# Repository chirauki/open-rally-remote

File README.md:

# Open Rally Remote

> Spanish version: [README.es.md](README.es.md).

An open-source Bluetooth handlebar remote for motorcycle navigation and digital roadbooks. The project aims to keep the unit compact, rugged, affordable, and buildable one unit at a time by individual makers.

## Designed with AI

This project is a demonstration that large language models and AI agents let a person design a product from scratch without the engineering background it would normally need. The remote started from the needs of a rider who is not an electronics, mechanical or firmware engineer. AI assistants (ChatGPT and Claude) designed it from there: the requirements, the CAD models, the circuit boards, the firmware, the bill of materials and this documentation.

The person sets the goals, makes the decisions, buys the parts and tests on the bench; the AI does the engineering work, checks its own designs in CAD, KiCad and on the bench, and records what has and has not been verified. The design history in [docs/](docs/) and the commit log show how each decision was reached.

## Project status

Requirements and the first-version concept are being defined. No hardware design or compatibility claim has been validated yet.

See the [project brief](docs/project-brief.md) for the current goals, proposed design, constraints, and development plan. The current [control mapping draft](docs/control-mapping.md) records proposed app profiles and the compatibility checks still needed. The [prototype plan](docs/prototype-plan.md) compares controller candidates and lays out a bench proof of concept. The [XIAO breadboard assembly guide](docs/breadboard-assembly.md) gives the wiring diagram for the temporary input fixture.

The proposed [firmware specification](docs/firmware-spec.md) defines the first BLE HID approach, input and gesture behavior, app-profile boundaries, bench validation, and the product requirement for phone-based BLE firmware updates.

The [development environment guide](docs/development-environment.md) explains how to set up Arduino IDE 2 for the purchased XIAO nRF52840, upload a smoke-test sketch, and use the Serial Monitor. The [mechanical CAD notes](docs/mechanical-concept.md) document the current NAVCOMM-referenced concept: a battery-powered remote that slides onto a base clamped to the bar, raised external controls, and 25 mm along the bar (since V0.33; NAVCOMM's 23 mm is a reference). V0.26 can be built without soldering: assembled boards, bought cables, a TPU keypad and a plug-in XIAO. The boards can also be ordered bare and soldered by hand, for much less ([ordering the boards](docs/bom.md#ordering-the-boards)). V0.27 changes the joystick board so the housing closes onto the stack in a straight line, which V0.26's [path check](docs/assembly-video-v0.26-checks.md) found it could not. V0.28 fits one base to both bar sizes and moves the vent to the battery cap. V0.29 drops the heat-set inserts, so the build needs no hot tool. V0.30 seals the cover with a foam strip, because the keypad sheet could not be squeezed enough by M2 screws, and V0.31 seals the battery cap the same way. V0.32 cuts the number of different parts to buy: a standard M3 × 20 lock screw, anti-rattle strips cut from a bike inner tube, and foam pads from the seal foam. V0.33 thickens the remote's 1 mm walls to 2 mm, outward, for falls and for watertight prints; the cavity does not change. V0.34 follows the first soldered USB-C board, whose receptacle sits 0.3 mm off the screw holes: the board slides on its rib onto square nuts, so the gasket sets its squeeze, and goes in upside down so a driver reaches its screws through the battery cap opening; and the foam seals take two layers of the thinner sheet that was bought. An [assembly video](docs/videos/complete-remote-v0.34-assembly.mp4) with a [path check](docs/assembly-video-v0.34-checks.md) shows the V0.34 steps with no collisions, and a [fitting video](docs/videos/usbc-mount-v0.34.mp4) shows the USB-C board step in detail.

The [battery study](docs/battery-study.md) compares battery options and settles on a removable remote with a fixed LiPo pouch, shared between bikes on a sliding dovetail base and charged off the bike (issue #1). V0.24 models it, V0.25 moves the pouch to a battery cap in the bottom end, and V0.26 fits it protection board up so its lead plugs straight into the control board; see the [mechanical CAD notes](docs/mechanical-concept.md). Nothing of it has been built or measured.

The [build guide](docs/build-guide.md) takes a builder from this repository to a finished remote, in order, with the catches found so far: minimum orders, packs and import charges. It has not been tried on a build yet. The [user manual](docs/user-manual.md) explains how to use the finished remote: charging, pairing, profiles and what each control does. The [bill of materials](docs/bom.md) lists every part for the bench prototype, the remote and the base, with sources. The [materials study](docs/materials-study.md) compares print materials against sun, rain, fuel, cold and falls, with quotes from EU print services; the material is not chosen yet. The [electronics assembly guide](docs/electronics-assembly.md) takes the bare boards through hand soldering, tests and conformal coating, step by step with images; it has not been tried on a build yet.

V0.31 to V0.34 have three KiCad boards, each with Gerbers, a BOM and a placement file for assembly: the [control board](electronics/control-pcb/README.md) (buttons, plug-in XIAO, charger, regulator, sockets), the [joystick board rev C](electronics/joystick-pcb-rev-c/README.md) and the [USB-C charging board rev B](electronics/usbc-pcb-rev-b/README.md). The control and joystick boards are ordered together as [one panel](electronics/panel-ctrl-joy/README.md). The [joystick board rev B](electronics/joystick-pcb-rev-b/README.md) belongs to V0.26, and the rev A [joystick](electronics/joystick-pcb/README.md) and [USB-C](electronics/usbc-pcb/README.md) boards to V0.23–V0.25. None has been built yet.

The [XIAO bench firmware](firmware/xiao-nrf52840/README.md) reads the breadboard switches and sends BLE HID keyboard keys. It reads the joystick center as a chord of the direction switches. It has three profiles, tested on Android: TerraPirata, a keyboard profile with held keys for DMD2, and a gestures profile for OsmAnd; holding the joystick center 5 s, releasing it, then pressing A, B or C chooses one. It has passed a first bench test on a XIAO with breadboard switches, paired with a phone. It has also been updated over BLE from an Android phone with the XIAO's factory bootloader, which accepts unsigned images and is not yet the product's update path. The battery firmware (level, charging, power off, auto-off and wake) is written and partly tested on USB; it has not run on a cell yet.

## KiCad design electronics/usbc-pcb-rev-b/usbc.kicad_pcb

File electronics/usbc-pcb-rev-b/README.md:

# USB-C Charging Board, Rev B (V0.26)

Rev B of the [USB-C charging board](../usbc-pcb/README.md) for the no-solder V0.26 remote ([spec](../../docs/superpowers/specs/2026-10-14-no-solder-assembly-design.md)). The GCT USB4736 receptacle, the two 5.1 kΩ CC pull-downs and the side-looking charge LED stay at their rev A positions against the rear wall. The changes:

- The wire pads become one JST SH-compatible 3-pin side-entry socket (J2, LCSC C2906269) behind the receptacle, opening into the remote toward the control board.
- The board is 16.0 mm deep instead of 13.6 mm, and the two M2 holes move from x = ±5.4 to ±7.0 mm, to make room for the socket. The CC resistors move beside the receptacle. `usbc_pcb` and `usbc_pcb_holes` in `mechanical/cad/complete-remote-v0.26.scad` follow.
- **Charge LED.** D1's anode goes to VBUS through R3 (1 kΩ); its cathode goes to J2 pin 3 and on to the charger's STAT pin on the control board. STAT is low only while the cell charges, so the LED lights only then, powered from the charger, not the cell. About 3 mA at 5 V. The firmware no longer drives it.

| J2 pin | Signal |
|---|---|
| 1 | VBUS |
| 2 | GND |
| 3 | LED cathode (to the charger's STAT) |

J2 has the same order as J3 on the control board, for a straight double-ended 3-pin JST SH cable. Check that the bought cable is straight.

The receptacle is in the JLCPCB library only through global sourcing (C9900206672), with no JLCPCB stock on 2026-10-14; on 2026-10-15 JLCPCB could not source it for an order. C9900206672 is the USB4736-GF-A without the gasket. Buy the USB4736-GF-A-KIT (receptacle and USBTJ-06 gasket) from TME or DigiKey and solder it by hand; leave J1 unselected in an assembly order. The gasket goes on after the receptacle is soldered.

## Next revision

The next revision is planned at 1.6 mm, with the rib lowered 0.4 mm. It should also power the LED from 3V3, so the firmware can use it as a status light without a charger, through a 4-pin J2. See the open unknowns in the [mechanical notes](../../docs/mechanical-concept.md#open-unknowns-before-printing).

## Receptacle footprint

`orr:GCT_USB4736` was drawn by hand from GCT's drawing USB4736, revision A, 9 April 2025, sheet 1, "Recommended PCB Layout". Checked against that drawing on 2026-10-14:

| Feature | Drawing | Footprint |
|---|---|---|
| Signal pads: width; centres across | 0.80 (B12, A12), 0.76 (B9, A9), 0.70 (A5, B5); ±2.75, ±1.52, ±0.50 | Same |
| Signal pads: length; distance from the PCB edge | 1.90; 5.50–7.40 (1.40 + 2.90 + 3.10) | Same. Until this check, the pads sat at 5.40–7.30 mm, 0.10 mm toward the edge |
| Shell slots: centres; drill; pad | ±4.895 (9.79 apart), 1.40 and 4.30 from the edge; 0.50 × 1.20; 1.10 × 1.80 | Same |
| Locating holes | Ø0.95, ±3.25 (6.50 apart), 4.30 from the edge | Same |
| Pin order, seen from the top | B12, B9, A5, B5, A9, A12, left to right | Same |
| Nose past the PCB edge | 1.70 (3.10 from the nose to the first shell slot, less 1.40) | 1.70 |

The terminal feet (bottom view: 2.20 to 2.60 mm behind the locating posts, so 6.50–6.90 mm from the edge) sit inside the pads either way. Check again against the footprint JLCPCB uses for the global-sourcing part (C9900206672) when ordering.

## Regenerating and checks

`gen_pcb.py` and `gen_sch.py` are shared with the control board: run `gen_pcb.py` with KiCad's Python, then the ERC, DRC and export commands in the [control board README](../control-pcb/README.md#regenerating), with `usbc` in place of `control`.

On 2026-10-14, again after the footprint fix: ERC 0 errors; DRC with schematic parity 0 errors and 0 unconnected pads (the remaining warnings say only that kicad-cli has no library tables).

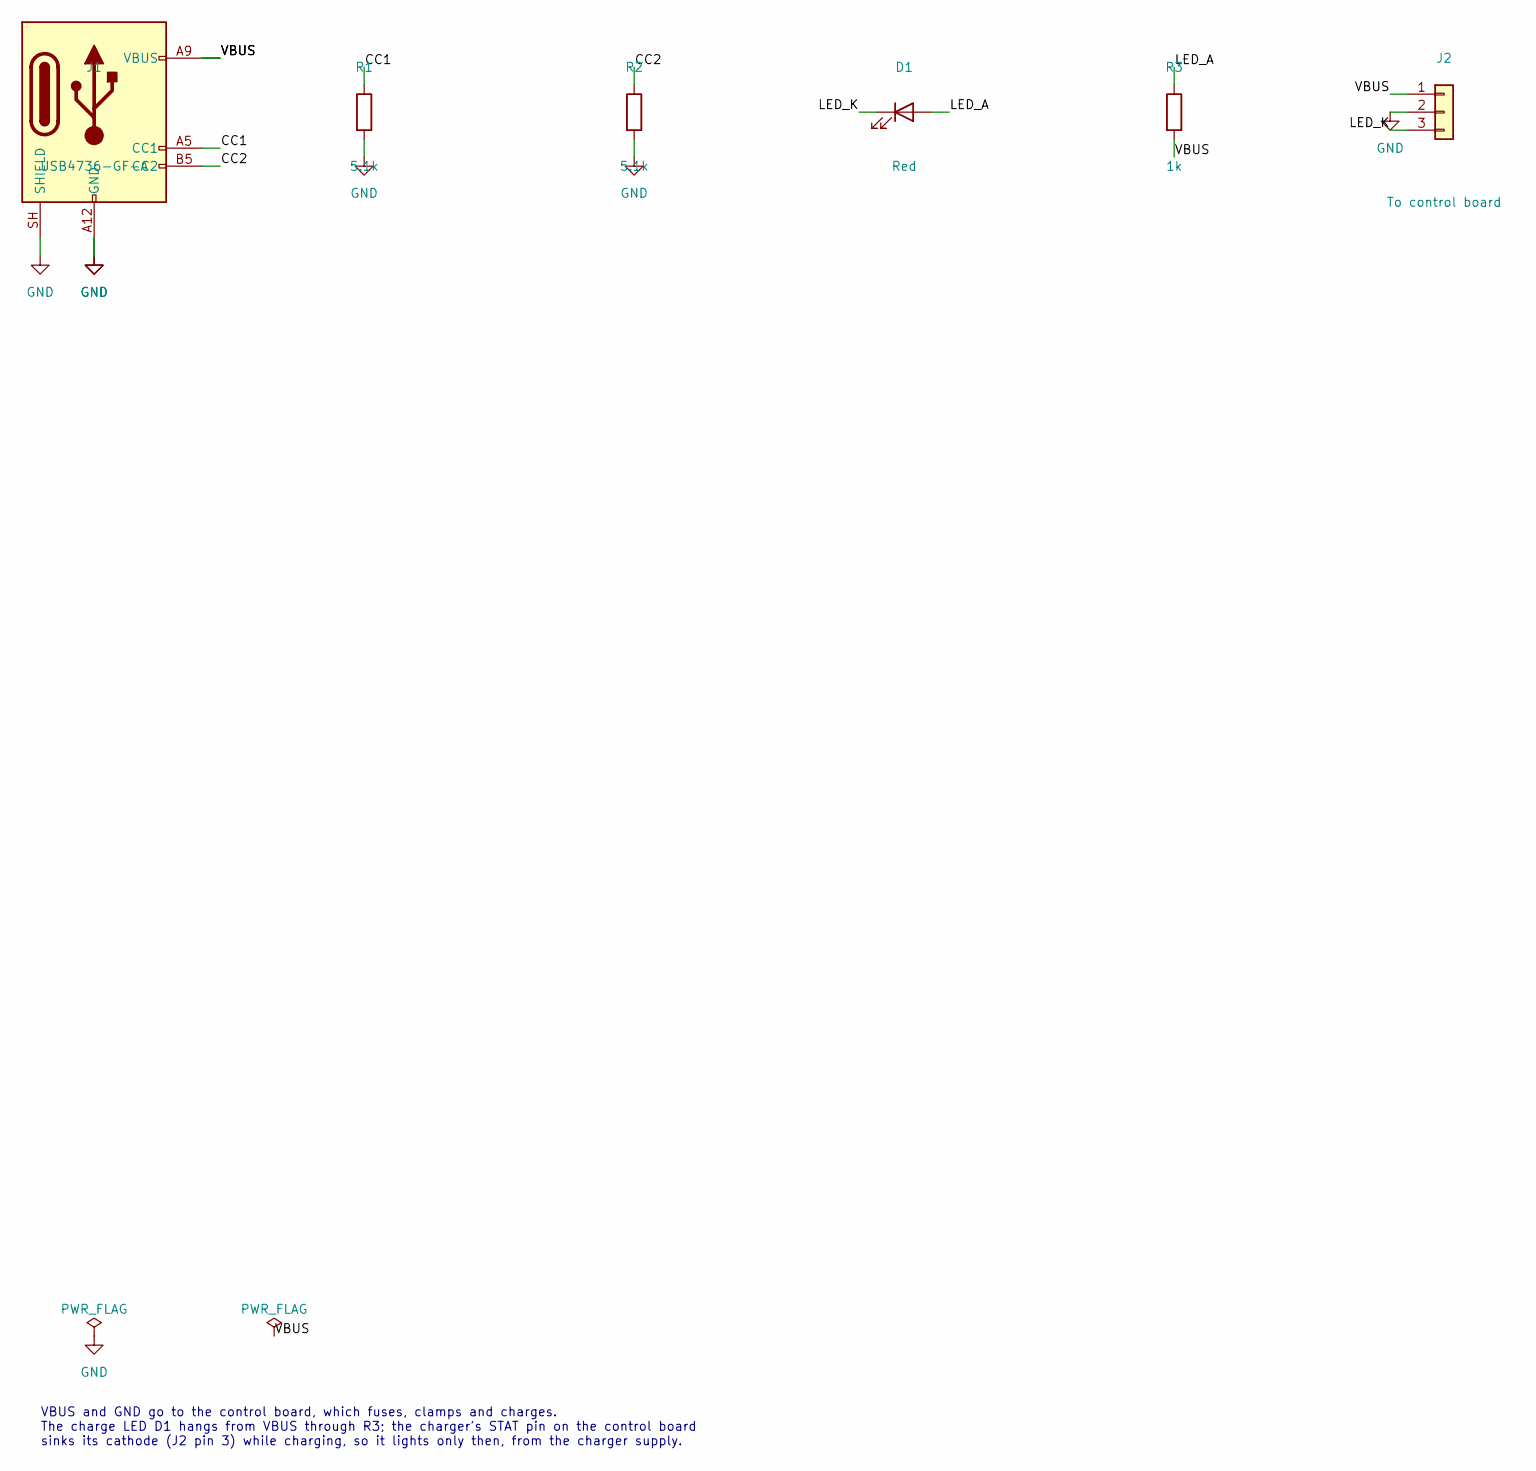
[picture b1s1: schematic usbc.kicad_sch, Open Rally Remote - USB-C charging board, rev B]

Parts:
D1: Red; LED_LiteOn_LTST-S270; MPN LTST-S270KRKT; LCSC C125114
J1: USB4736-GF-A; GCT_USB4736; MPN USB4736-GF-A-KIT; LCSC C9900206672
J2: To control board; JST_SH_SM03B-SRSS-TB_1x03-1MP_P1.00mm_Horizontal; MPN 1.0-3P WT; LCSC C2906269
R1, R2: 5.1k; R_0603_1608Metric; MPN 0603WAF5101T5E; LCSC C23186
R3: 1k; R_0603_1608Metric; MPN RC0603FR-071KL; LCSC C22548

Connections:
/CC1: J1.A5 (CC1), R1.1
/CC2: J1.B5 (CC2), R2.1
/LED_A: D1.2 (A), R3.1
/LED_K: D1.1 (K), J2.3
/VBUS: J1.A9 (VBUS), J1.B9 (VBUS), J2.1, R3.2
GND: J1.A12 (GND), J1.B12 (GND), J1.SH (SHIELD), J2.2, R1.2, R2.2

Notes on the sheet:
VBUS and GND go to the control board, which fuses, clamps and charges. The charge LED D1 hangs from VBUS through R3; the charger's STAT pin on the control board sinks its cathode (J2 pin 3) while charging, so it lights only then, from the charger supply.

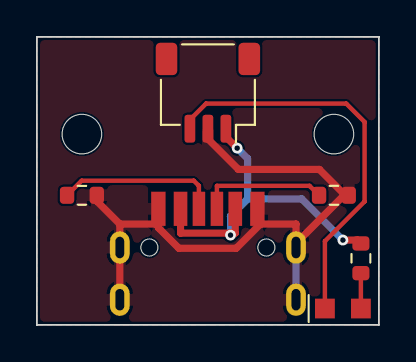
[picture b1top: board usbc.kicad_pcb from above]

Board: 2 copper layers, 19.0 x 16.0 mm, 8 parts (0 on the bottom side), 6 nets.

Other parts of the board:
H1, H2: M2; MountingHole_2.2mm_M2

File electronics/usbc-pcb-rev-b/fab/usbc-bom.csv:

"Reference","Value","Footprint","Manufacturer","MPN","LCSC","Qty"
"D1","Red","orr:LED_LiteOn_LTST-S270","Lite-On","LTST-S270KRKT","C125114","1"
"J1","USB4736-GF-A","orr:GCT_USB4736","GCT","USB4736-GF-A-KIT","C9900206672","1"
"J2","To control board","Connector_JST:JST_SH_SM03B-SRSS-TB_1x03-1MP_P1.00mm_Horizontal","","1.0-3P WT","C2906269","1"
"R1,R2","5.1k","Resistor_SMD:R_0603_1608Metric","UNI-ROYAL","0603WAF5101T5E","C23186","2"
"R3","1k","Resistor_SMD:R_0603_1608Metric","YAGEO","RC0603FR-071KL","C22548","1"

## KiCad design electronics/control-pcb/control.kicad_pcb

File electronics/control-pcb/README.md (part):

# Control Board (V0.26)

The control board sits behind the upper facet of the V0.26 remote. Its front carries the three button switches; its back carries the XIAO nRF52840 in two female headers, the LiPo charger, the 3.3 V regulator and the connectors for the joystick board, the USB-C charging board and the battery. It can be ordered assembled, so the builder does not solder, or bare, for the builder to solder by hand; see [Ordering the boards](../../docs/bom.md#ordering-the-boards). `fab/economic-bottom/` holds the BOM and placement for JLCPCB Economic assembly of the back side only; the builder then solders the switches and the headers. The design is in the [no-solder assembly spec](../../docs/superpowers/specs/2026-10-14-no-solder-assembly-design.md).

## Parts

Checked in the JLCPCB parts library on 2026-10-14. Stock and prices change; check again before ordering. "Extended" parts add JLCPCB's extended-part fee per unique part.

| Function | Part | LCSC | Library | Stock | Notes |
|---|---|---|---|---|---|
| Button switches ×3 | C&K KSC221JLFS | C221726 | Extended | 17,354 | Same switch as the joystick board |
| LiPo charger | Microchip MCP73831T-2ACI/OT, SOT-23-5 | C424093 | Extended | 11,479 | 4.20 V. Charge current 1000 V / R_PROG: 10 kΩ gives 100 mA. STAT is low while charging, high when done, high-impedance with no input |
| 3.3 V regulator | TI TPS70933DBVR, SOT-23-5 | C89347 | Extended | 45,791 | 1 µA quiescent, 2.7–30 V input, reverse current protection ([TI](https://www.ti.com/product/TPS709)), 300 mV typical dropout |
| Battery reverse-polarity protection | AO3401A P-MOSFET, SOT-23 | C15127 | Basic | 605,007 | In the battery line, conducting both ways when the cell is the right way round |
| 5 V input fuse | Bourns MF-MSMF050-2, 1812 PTC | C17313 | — | — | As on the V0.23 joystick board |
| 5 V input TVS | Littelfuse SMBJ5.0A | C83333 | Extended | 45,298 | 65 µA leakage at 5 V; the other SMBJ5.0A listed, C78423, leaks 800 µA (both checked 2026-10-15) |
| Joystick socket (5-pin) | JST SH-compatible "1.0-5P WT", side entry, SMD | C2906271 | Extended | 14,999 | Genuine SM05B-SRSS-TB: C136657, 158 in stock |
| USB-C board socket (3-pin) | JST SH-compatible "1.0-3P WT", side entry, SMD | C2906269 | Extended | 13,209 | Genuine SM03B-SRSS-TB: none in stock |
| Battery socket (2-pin) | JST B2B-PH-SM4-TB(LF)(SN), top entry, SMD | C160352 | Extended | 89,576 | Side entry (S2B-PH-SM4-TB, C295747) was dropped: its plug had no room toward the wall |
| XIAO headers ×2 | 2.54 mm 1×7 female, 5.7 mm high, through hole | C55218877 | Extended | 644 | Standard 8.5 mm alternative: C54876729, 2,409 in stock |

The XIAO nRF52840 is in the JLCPCB library (C37327670 and others) with no stock, so the XIAO is bought separately with pins and plugged in. The PTC and TVS stock was not rechecked.

### USB-C charging receptacle

The GCT USB4736-GF-A is listed in the JLCPCB library only through global sourcing (C9900206672), with no JLCPCB stock on 2026-10-14. On 2026-10-15 JLCPCB could not source it for an order. C9900206672 is the receptacle without its USBTJ-06 gasket; buy the USB4736-GF-A-KIT (receptacle and gasket) from TME or DigiKey and solder it by hand. No other sealed receptacle that keeps the CC pins was found in the library.

### Cables

Retail, pre-crimped at both ends. Amazon listings were not found through web search; that does not mean there are none.

| Cable | Source found | Length |
|---|---|---|
| JST SH-style 5-pin, female–female, 1 mm | [Pololu 5-pin JST SH-style cables](https://www.pololu.com/category/350/5-pin-jst-sh-style-cables) | 10 cm shortest |
| JST SH-style 3-pin, female–female, 1 mm | Pololu's 3-pin range (not checked) | 10 cm shortest |
| JST PH 2-pin extension, male–female | [BerryBase](https://www.berrybase.de/en/extension-cable-2-pin-jst-ph-2.0mm-male-female-awg24-50cm) | 50 cm; shorter not found |

The routes need about 3 cm (joystick) and 4 cm (USB-C). The spare length of a 10 cm cable has to be stowed inside; the CAD checks this. The "1.0 WT" sockets are sold as JST SH compatible; check that a Pololu plug latches in one before ordering the board.

### XIAO pins

The board position depends on the pre-soldered XIAO's header: the plastic spacer height and the pin length below it. Neither is published by Seeed; measure them on the bench XIAO. A pin longer than the 5.7 mm socket is deep holds the XIAO higher than the spacer would.

## Circuit decisions

- **STAT to the XIAO.** The MCP73831's STAT is a three-state push-pull output: low while charging, high (about VDD − 0.4 V, so about 4.6 V from USB-C) when charging ends, high impedance with no input. D8 reads it through a 100 kΩ / 150 kΩ divider: at most about 2.8 V. The charge LED on the USB-C board hangs from VBUS to STAT through its resistor, so it lights only while STAT is low (charging).
- **VBUS to the XIAO.** D9 reads VBUS through a 100 kΩ / 150 kΩ divider: 3.0 V at 5.0 V, 3.15 V at 5.25 V. (Until the 2026-10-15 review it was 100k/200k, 3.3–3.5 V: with a low cell the XIAO's 3V3 rail sits near 3.0 V, and the nRF52840's pin limit is VDD + 0.3 V.)
- **Battery voltage.** A0 reads the cell through a 1 MΩ / 1 MΩ divider with 100 nF to ground: 2.1 V at 4.2 V, about 2 µA drawn from the cell.
- **Different socket sizes.** The joystick socket has 5 pins, the USB-C one 3 and the battery one is a 2-pin PH: no cable fits the wrong socket.

## Next revision

The next revision should add an N-MOSFET from the charging LED's cathode to GND, driven by D7, and a 4-pin J3 that also carries 3V3 to the USB-C board, so the firmware can pulse the LED as a status light without a charger. STAT keeps lighting it while charging. See the open unknowns in the [mechanical notes](../../docs/mechanical-concept.md#open-unknowns-before-printing).

## Review

An independent review on 2026-10-15 (a fresh Claude session reading the files and the TI SBVS186H, Microchip DS20001984H and AOS AO3401A datasheets) found no critical defect. It changed R3/R5 to 150k, C3/C4 to 4.7 µF (the TPS709 needs 1.5 µF effective at its output) and D1 to the low-leakage SMBJ5.0A, and raised the open points listed under Checks. Not verified by it: the XIAO regulator's reverse leakage and its 3V3-rail capacitance, the System OFF current, the KSC2 internal contact pairs, and the LED's cathode pad against the Lite-On drawing.

## Board

A 21.4 × 49 mm, 1.6 mm two-layer board, notched round the six upper cover-screw bosses so it lifts out with the cover (see `ctrl_pcb_*` in `mechanical/cad/complete-remote-v0.26.scad`). Board x is the CAD's Z − 11.5, board y is 16.5 − Y.

- **Front** (toward the cover): SW1–SW3 under keys A, B and C, at Y = 33, 15 and −3. Each switch uses a diagonal pad pair, as on the joystick board.
- **Back:** the two XIAO headers (pin 1 at the XIAO's USB-C end, D0–D6 on the −Z side), the charger, the regulator, Q1 and the dividers under the XIAO, J3 (USB-C board, side entry, opening down toward the USB-C board's socket) and J5 (battery, top entry: the pouch lead plugs in from behind, toward the pouch) at the top, J4 (joystick) at the bottom, F1 and D1 between them.
- **Holes:** two M2 holes onto the button plate standoffs, at Y = 24 and Y = 6, 3.95 mm either side of the centre line so the standoffs clear the key holes in the button plate.
- **Routing:** Freerouting 1.9.0, with ground pours on both layers. Track keep-outs round the notches hold the 0.3 mm edge clearance.

## Regenerating

`design.py` holds the outline, placement and nets. From this directory:

```
/Applications/KiCad/KiCad.app/Contents/Frameworks/Python.framework/Versions/Current/bin/python3 gen_pcb.py
```

`gen_pcb.py` places the parts, routes the board with Freerouting (`FREEROUTING_JAR`, default `~/.arduino-orr/tools/freerouting-1.9.0.jar`; Freerouting 2.x needs Java 25), fills the pours, writes `control.kicad_pcb` and calls `gen_sch.py` for `control.kicad_sch`. Freerouting may route differently on each run. Then check and export:

```
K=/Applications/KiCad/KiCad.app/Contents/MacOS/kicad-cli
$K sch erc --severity-all control.kicad_sch
$K pcb drc --schematic-parity --severity-all control.kicad_pcb
$K pcb export gerbers --layers F.Cu,B.Cu,F.Paste,B.Paste,F.SilkS,B.SilkS,F.Mask,B.Mask,Edge.Cuts --subtract-soldermask -o fab/gerbers/ control.kicad_pcb
$K pcb export drill --format excellon --excellon-separate-th --generate-map --map-format gerberx2 -o fab/gerbers/ control.kicad_pcb
$K sch export bom --fields 'Reference,Value,Footprint,Manufacturer,MPN,LCSC,${QUANTITY}' --labels 'Reference,Value,Footprint,Manufacturer,MPN,LCSC,Qty' --group-by 'Value,Footprint' --exclude-dnp -o fab/control-bom.csv control.kicad_sch
$K pcb export pos --format csv --units mm --side both --exclude-dnp -o fab/control-pos.csv control.kicad_pcb
python3 jlc_cpl.py
```

## Checks

Run on 2026-10-14, and again on 2026-10-15 after the J5 polarity marks and the review fixes (R3/R5 150k, C3/C4 4.7 µF, D1 C83333); same results, Freerouting routed it again:

- ERC: 0 errors. The 72 warnings say only that kicad-cli has no global symbol and footprint library tables configured.
- DRC with schematic parity: 0 errors, 0 unconnected pads, 0 footprint errors; the 22 warnings are the same library-table notice.
- **Battery plugged in reversed:** without USB, Q1's body diode is reverse-biased and its gate-source voltage stays at 0 V, so no current flows. With USB plugged in, the charger raises BAT_SYS until Q1 turns on and its preconditioning current (about 10 mA) flows into the reversed cell: not dangerous, but the cell slowly discharges and the charge LED lights. Unplug and turn the plug round.
- **XIAO's own USB-C plugged in with the battery in:** the XIAO's regulator drives 3V3 too; the TPS70933's reverse current protection stops current flowing back into it.
- **Charger with no battery:** the MCP73831 holds BAT_SYS near 4.2 V, so the remote runs on USB power alone. With no cell, the charger may cycle, and the charge LED and D8 may flicker; this was not checked.
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
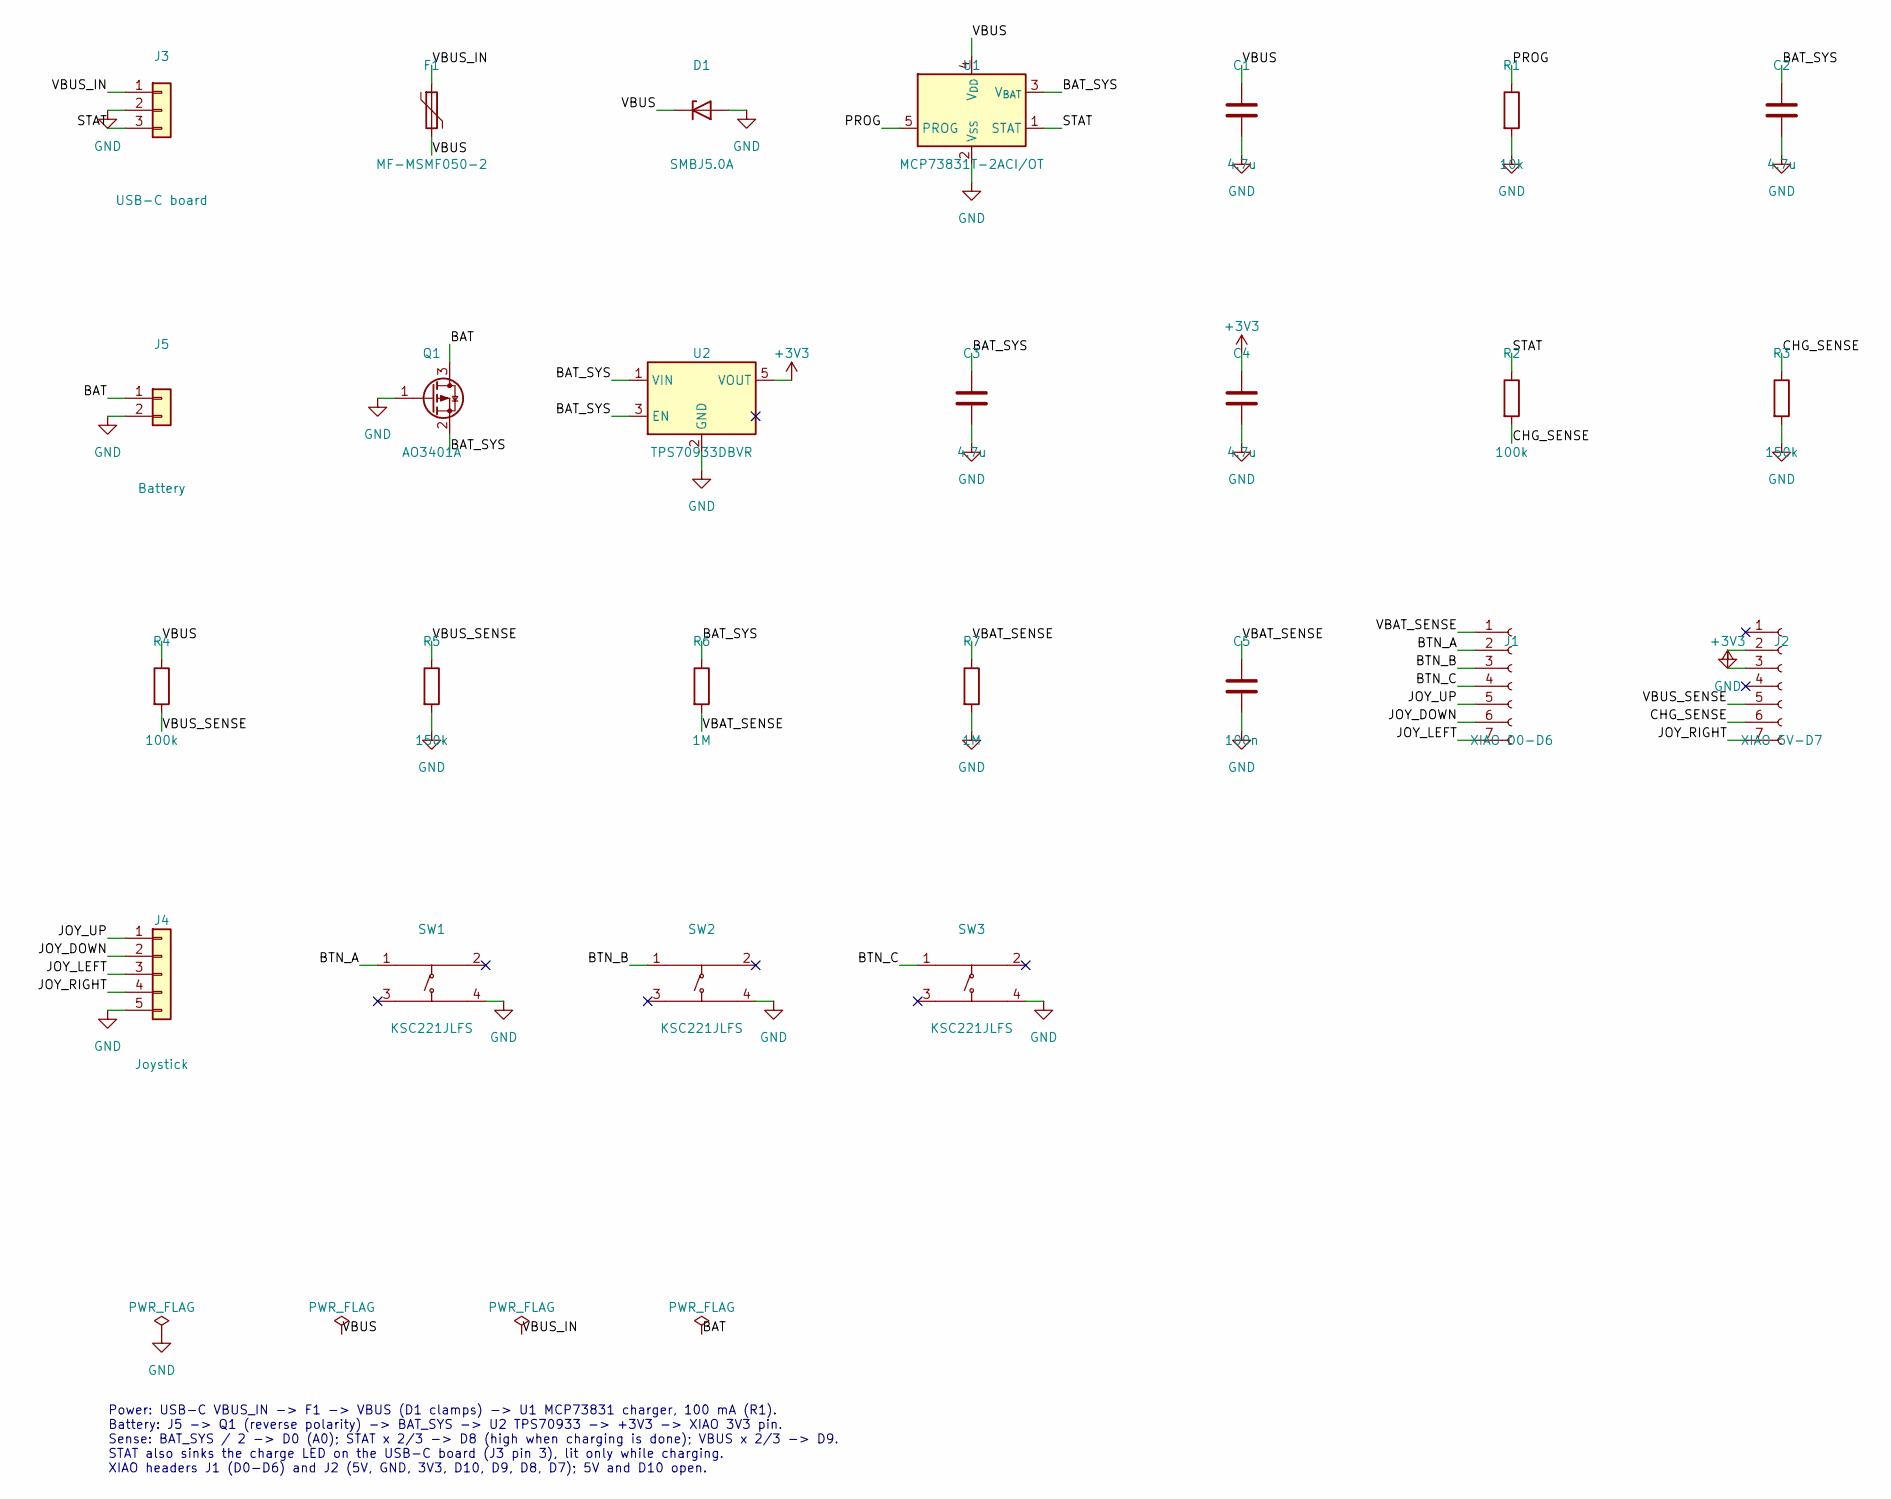
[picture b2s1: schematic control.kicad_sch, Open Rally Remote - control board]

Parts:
C1, C2, C3, C4: 4.7u; C_0603_1608Metric; MPN CL10A475KO8NNNC; LCSC C19666
C5: 100n; C_0603_1608Metric; MPN CC0603KRX7R9BB104; LCSC C14663
D1: SMBJ5.0A; D_SMB; MPN SMBJ5.0A; LCSC C83333
F1: MF-MSMF050-2; Fuse_1812_4532Metric; MPN MF-MSMF050-2; LCSC C17313
J1: XIAO D0-D6; PinSocket_1x07_P2.54mm_Vertical; MPN PM2.54-1x7PZZ-H5.7; LCSC C55218877
J2: XIAO 5V-D7; PinSocket_1x07_P2.54mm_Vertical; MPN PM2.54-1x7PZZ-H5.7; LCSC C55218877
J3: USB-C board; JST_SH_SM03B-SRSS-TB_1x03-1MP_P1.00mm_Horizontal; MPN 1.0-3P WT; LCSC C2906269
J4: Joystick; JST_SH_SM05B-SRSS-TB_1x05-1MP_P1.00mm_Horizontal; MPN 1.0-5P WT; LCSC C2906271
J5: Battery; JST_PH_B2B-PH-SM4-TB_1x02-1MP_P2.00mm_Vertical; MPN B2B-PH-SM4-TB(LF)(SN); LCSC C160352
Q1: AO3401A; SOT-23; MPN AO3401A; LCSC C15127
R1: 10k; R_0603_1608Metric; MPN 0603WAF1002T5E; LCSC C25804
R2, R4: 100k; R_0603_1608Metric; MPN 0603WAF1003T5E; LCSC C25803
R3, R5: 150k; R_0603_1608Metric; MPN 0603WAF1503T5E; LCSC C22807
R6, R7: 1M; R_0603_1608Metric; MPN 0603WAF1004T5E; LCSC C22935
SW1, SW2, SW3: KSC221JLFS; KSC2_SMD_6.2x6.2mm; MPN KSC221JLFS; LCSC C221726
U1: MCP73831T-2ACI/OT; SOT-23-5; MPN MCP73831T-2ACI/OT; LCSC C424093
U2: TPS70933DBVR; SOT-23-5; MPN TPS70933DBVR; LCSC C89347

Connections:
+3V3: C4.1, J2.3, U2.5 (VOUT)
/BAT: J5.1, Q1.3 (D)
/BAT_SYS: C2.1, C3.1, Q1.2 (S), R6.1, U1.3 (V_{BAT}), U2.1 (VIN), U2.3 (EN)
/BTN_A: J1.2, SW1.1
/BTN_B: J1.3, SW2.1
/BTN_C: J1.4, SW3.1
/CHG_SENSE: J2.6, R2.2, R3.1
/JOY_DOWN: J1.6, J4.2
/JOY_LEFT: J1.7, J4.3
/JOY_RIGHT: J2.7, J4.4
/JOY_UP: J1.5, J4.1
/PROG: R1.1, U1.5 (PROG)
/STAT: J3.3, R2.1, U1.1 (STAT)
/VBAT_SENSE: C5.1, J1.1, R6.2, R7.1
/VBUS: C1.1, D1.1 (K), F1.2, R4.1, U1.4 (V_{DD})
/VBUS_IN: F1.1, J3.1
/VBUS_SENSE: J2.5, R4.2, R5.1
GND: C1.2, C2.2, C3.2, C4.2, C5.2, D1.2 (A), J2.2, J3.2, J4.5, J5.2, Q1.1 (G), R1.2, R3.2, R5.2, R7.2, SW1.4, SW2.4, SW3.4, U1.2 (V_{SS}), U2.2 (GND)

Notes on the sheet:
Power: USB-C VBUS_IN -> F1 -> VBUS (D1 clamps) -> U1 MCP73831 charger, 100 mA (R1). Battery: J5 -> Q1 (reverse polarity) -> BAT_SYS -> U2 TPS70933 -> +3V3 -> XIAO 3V3 pin. Sense: BAT_SYS / 2 -> D0 (A0); STAT x 2/3 -> D8 (high when charging is done); VBUS x 2/3 -> D9. STAT also sinks the charge LED 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

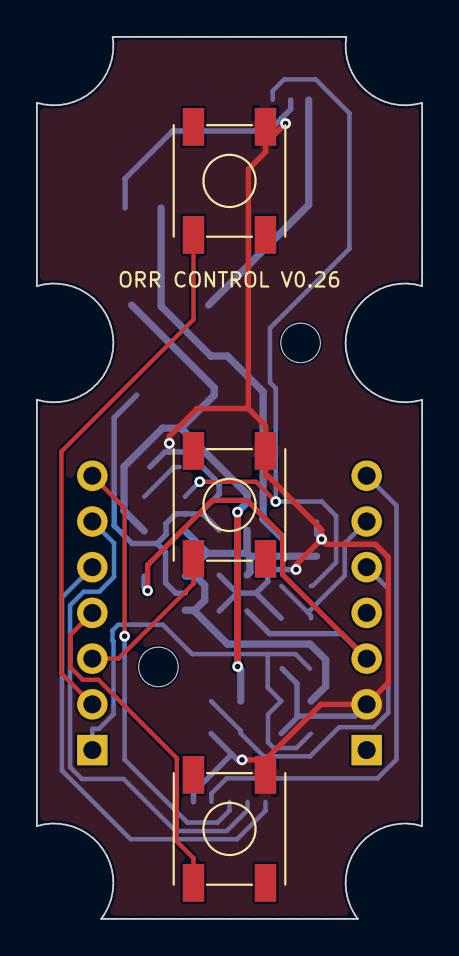
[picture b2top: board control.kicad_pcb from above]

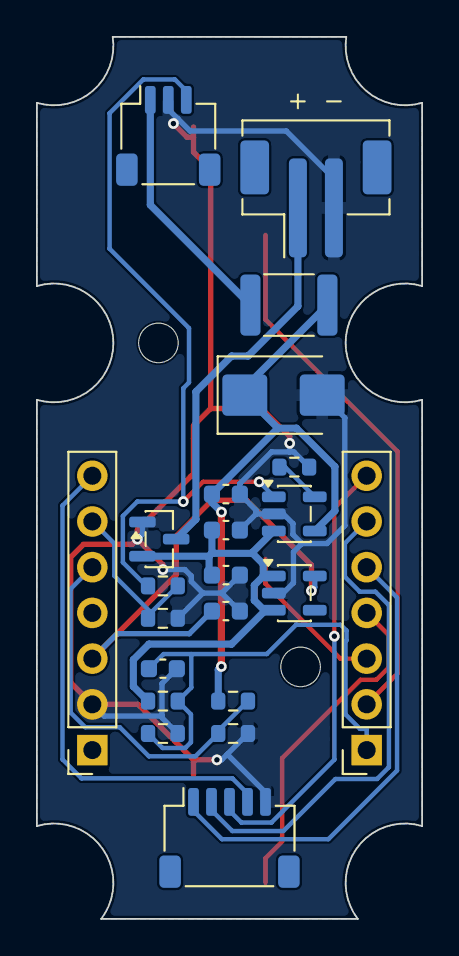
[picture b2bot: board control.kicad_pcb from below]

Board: 2 copper layers, 21.4 x 49.0 mm, 27 parts (22 on the bottom side), 18 nets.

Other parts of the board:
H1, H2: M2; Standoff_M2_PCB

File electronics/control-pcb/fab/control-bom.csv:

"Reference","Value","Footprint","Manufacturer","MPN","LCSC","Qty"
"C1-C4","4.7u","Capacitor_SMD:C_0603_1608Metric","Samsung","CL10A475KO8NNNC","C19666","4"
"C5","100n","Capacitor_SMD:C_0603_1608Metric","Yageo","CC0603KRX7R9BB104","C14663","1"
"D1","SMBJ5.0A","Diode_SMD:D_SMB","Littelfuse","SMBJ5.0A","C83333","1"
"F1","MF-MSMF050-2","Fuse:Fuse_1812_4532Metric","Bourns","MF-MSMF050-2","C17313","1"
"J1","XIAO D0-D6","Connector_PinSocket_2.54mm:PinSocket_1x07_P2.54mm_Vertical","","PM2.54-1x7PZZ-H5.7","C55218877","1"
"J2","XIAO 5V-D7","Connector_PinSocket_2.54mm:PinSocket_1x07_P2.54mm_Vertical","","PM2.54-1x7PZZ-H5.7","C55218877","1"
"J3","USB-C board","Connector_JST:JST_SH_SM03B-SRSS-TB_1x03-1MP_P1.00mm_Horizontal","","1.0-3P WT","C2906269","1"
"J4","Joystick","Connector_JST:JST_SH_SM05B-SRSS-TB_1x05-1MP_P1.00mm_Horizontal","","1.0-5P WT","C2906271","1"
"J5","Battery","Connector_JST:JST_PH_B2B-PH-SM4-TB_1x02-1MP_P2.00mm_Vertical","JST","B2B-PH-SM4-TB(LF)(SN)","C160352","1"
"Q1","AO3401A","Package_TO_SOT_SMD:SOT-23","Alpha & Omega","AO3401A","C15127","1"
"R1","10k","Resistor_SMD:R_0603_1608Metric","UNI-ROYAL","0603WAF1002T5E","C25804","1"
"R2,R4","100k","Resistor_SMD:R_0603_1608Metric","UNI-ROYAL","0603WAF1003T5E","C25803","2"
"R3,R5","150k","Resistor_SMD:R_0603_1608Metric","UNI-ROYAL","0603WAF1503T5E","C22807","2"
"R6,R7","1M","Resistor_SMD:R_0603_1608Metric","UNI-ROYAL","0603WAF1004T5E","C22935","2"
"SW1-SW3","KSC221JLFS","orr:KSC2_SMD_6.2x6.2mm","C&K","KSC221JLFS","C221726","3"
"U1","MCP73831T-2ACI/OT","Package_TO_SOT_SMD:SOT-23-5","Microchip","MCP73831T-2ACI/OT","C424093","1"
"U2","TPS70933DBVR","Package_TO_SOT_SMD:SOT-23-5","TI","TPS70933DBVR","C89347","1"

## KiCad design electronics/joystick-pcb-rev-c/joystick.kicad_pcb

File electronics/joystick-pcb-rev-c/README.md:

# Joystick Board, Rev C (V0.27)

Rev C of the joystick board, for V0.27. It is [rev B](../joystick-pcb-rev-b/README.md) with three changes, so the housing can close onto the stack, and the cover come off, in a straight line along the remote's X axis ([V0.27 changes from V0.26](../../docs/mechanical-concept.md#v027-changes-from-v026-still-current)):

- The two notches toward the fold (board y = −11.0) become slots running 3.0 mm down the facet (`SLOT` in `design.py`, `joy_pcb_slot` in the CAD). The lower cover bosses slide that way, 0.34 mm per millimetre, as the housing moves along X.
- The two standoff holes move to the lower half, at (±6.5, 6.4) in board coordinates. The upper half has no room for a screw between the switches and the slots.
- J1 moves from (1.0, 7.4) to (0.0, 7.4), to pass between the two screw heads.

The switches, the nets and the J1 pinout are those of rev B:

| J1 pin | Signal |
|---|---|
| 1 | UP |
| 2 | DOWN |
| 3 | LEFT |
| 4 | RIGHT |
| 5 | GND |

J1 has the same order as J4 on the control board, so a straight double-ended 5-pin JST SH cable (pin 1 to pin 1) joins them. Check that the bought cable is straight and not reversed before fitting it.

## Clearances

Board coordinates, mm, from `design.py` and the KiCad footprints:

| Between | Clearance |
|---|---|
| Slot edge and the nearest switch pad | 0.67 |
| Standoff (Ø3.6) and the nearest switch pad | 0.82 |
| Standoff and the nearest switch body | 1.35 |
| Standoff courtyard (R1.9) and the side-switch and J1 courtyards | 0.2 |
| Screw head (Ø3.5) and J1, each side | 0.35 |
| Standoff and the lower notch edge | 0.37 |

## Regenerating and checks

`design.py` builds the outline with the slots and holds the placement and nets. `gen_pcb.py` and `gen_sch.py` are shared with the control board: run `gen_pcb.py` with KiCad's Python, then the ERC, DRC and export commands in the [control board README](../control-pcb/README.md#regenerating), with `joystick` in place of `control`. The rear render is `kicad-cli pcb render --side bottom --width 1200 --height 900 -o fab/render-back.png joystick.kicad_pcb`.

On 2026-10-14: ERC 0 errors (the 9 warnings say only that kicad-cli has no library tables); DRC with schematic parity 0 errors and 0 unconnected pads (one library-table warning). Placing the standoffs at (±6.8, 6.0) first gave two courtyard overlaps with the side switches; (±6.5, 6.4) clears them. Full assembly is double-sided: switches on the front, the socket on the rear. `fab/economic-bottom/` holds the BOM and placement for JLCPCB Economic assembly of the rear side only (J1); the builder then solders the switches. The board can also be ordered bare and soldered by hand; see [Ordering the boards](../../docs/bom.md#ordering-the-boards). Check the parts' rotations in JLCPCB's placement preview.

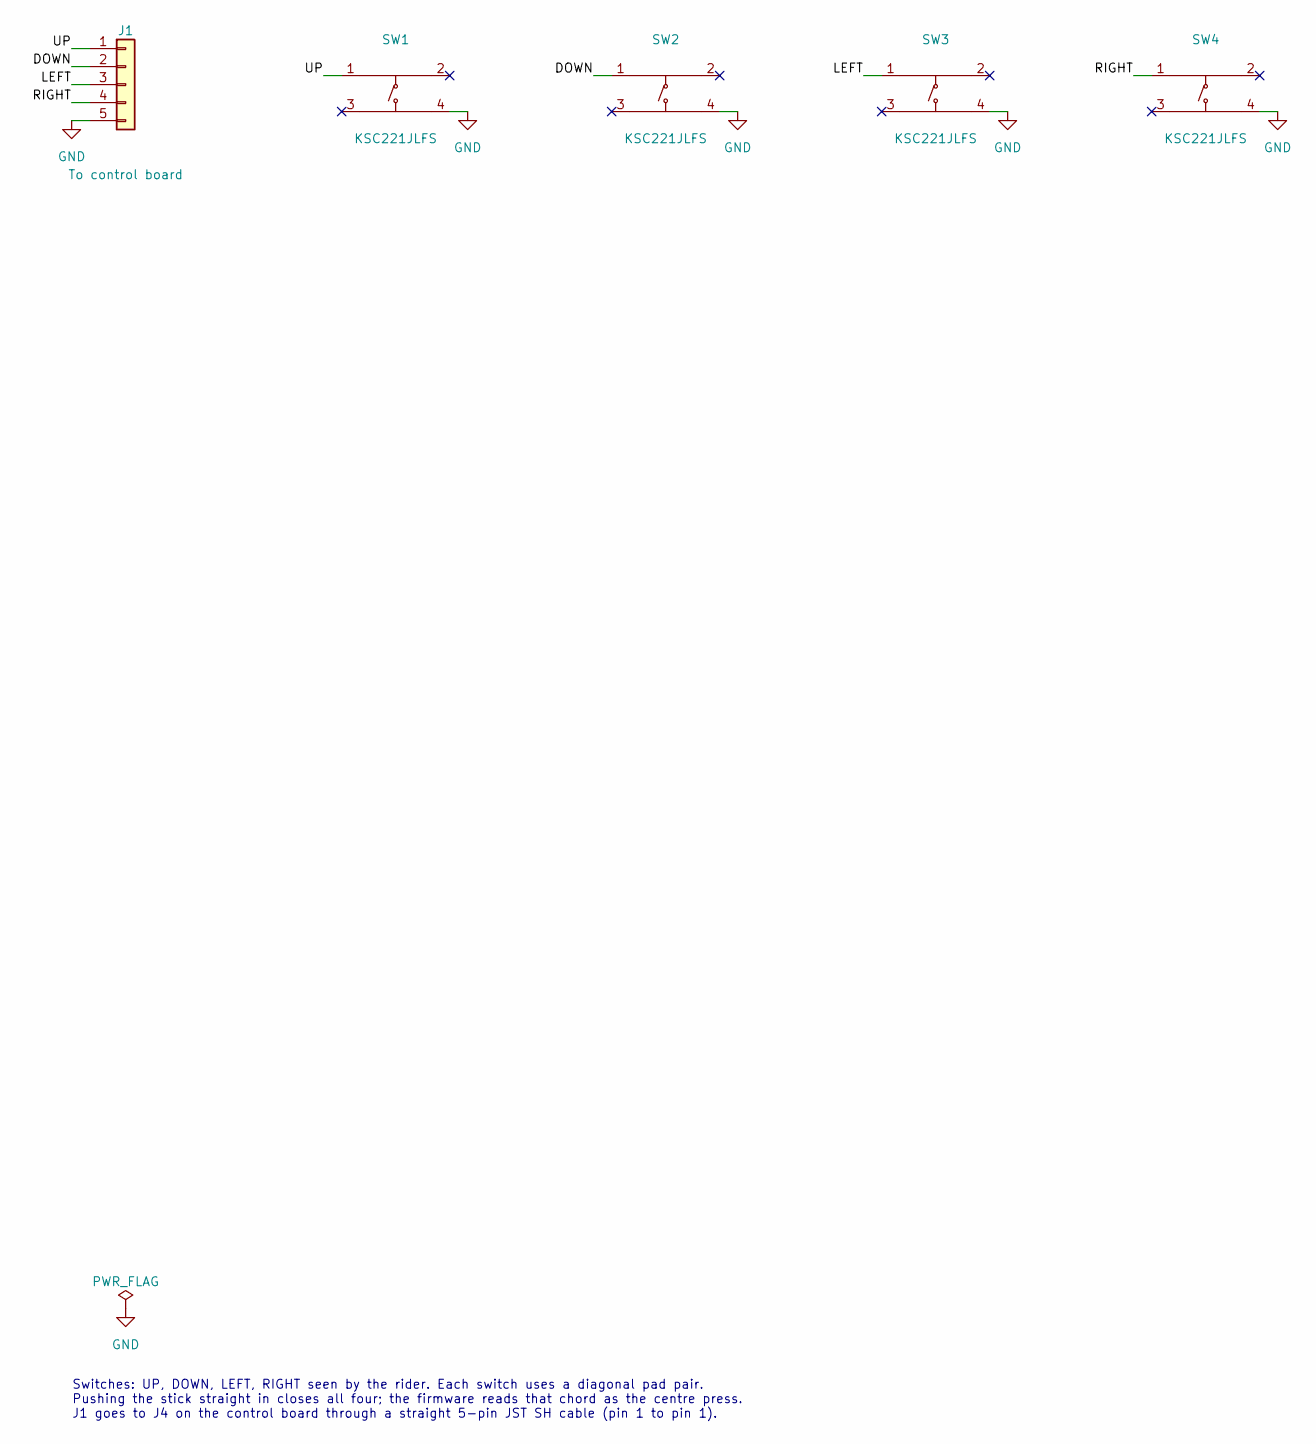
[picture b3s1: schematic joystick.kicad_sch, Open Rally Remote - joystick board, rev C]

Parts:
J1: To control board; JST_SH_SM05B-SRSS-TB_1x05-1MP_P1.00mm_Horizontal; MPN 1.0-5P WT; LCSC C2906271
SW1, SW2, SW3, SW4: KSC221JLFS; KSC2_SMD_6.2x6.2mm; MPN KSC221JLFS; LCSC C221726

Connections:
/DOWN: J1.2, SW2.1
/LEFT: J1.3, SW3.1
/RIGHT: J1.4, SW4.1
/UP: J1.1, SW1.1
GND: J1.5, SW1.4, SW2.4, SW3.4, SW4.4

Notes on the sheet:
Switches: UP, DOWN, LEFT, RIGHT seen by the rider. Each switch uses a diagonal pad pair. Pushing the stick straight in closes all four; the firmware reads that chord as the centre press. J1 goes to J4 on the control board through a straight 5-pin JST SH cable (pin 1 to pin 1).

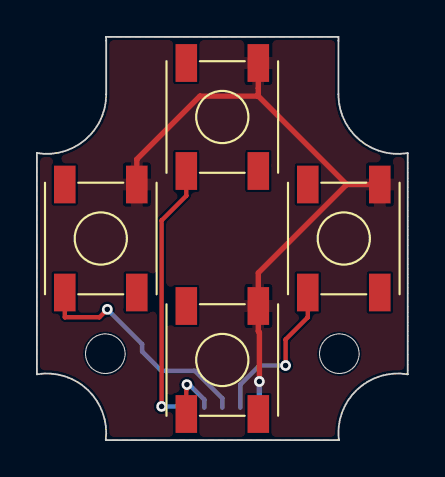
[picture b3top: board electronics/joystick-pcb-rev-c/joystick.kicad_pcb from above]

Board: 2 copper layers, 20.6 x 22.4 mm, 7 parts (1 on the bottom side), 5 nets.

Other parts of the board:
H1, H2: M2; Standoff_M2_PCB

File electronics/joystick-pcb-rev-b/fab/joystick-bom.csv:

"Reference","Value","Footprint","Manufacturer","MPN","LCSC","Qty"
"J1","To control board","Connector_JST:JST_SH_SM05B-SRSS-TB_1x05-1MP_P1.00mm_Horizontal","","1.0-5P WT","C2906271","1"
"SW1-SW4","KSC221JLFS","orr:KSC2_SMD_6.2x6.2mm","C&K","KSC221JLFS","C221726","4"

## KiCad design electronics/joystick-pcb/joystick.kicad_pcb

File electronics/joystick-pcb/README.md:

# Joystick PCB — V0.23

The joystick PCB carries the four C&K KSC2 switches under the stick's cross disc, and the 5 V input protection for the whole remote. It fits the V0.23 enclosure ([CAD](../../mechanical/cad/complete-remote-v0.23.scad), [notes](../../docs/mechanical-concept.md)).

Status: designed and checked in KiCad (ERC, DRC and schematic parity clean). Not yet built.

## Board

- Two layers, 1.6 mm FR-4, 1 oz copper. Ground pour on both sides.
- Outline 20.6 × 22.4 mm, with a 3.3 mm radius notch at each corner for the lower cover-screw bosses. The same numbers are in the CAD (`joy_pcb_hx`, `joy_pcb_hy`, `joy_pcb_notch_r`).
- Rules: 0.2 mm clearance, 0.25 mm signal tracks, 0.8 mm supply tracks, 0.6/0.3 mm vias, 0.3 mm copper to edge. These are within standard JLCPCB and PCBWay limits.
- Two Ø2.2 mm holes for M2 × 8 button-head screws into the joystick plate standoffs. The head must be no more than Ø3.5 × 1.1 mm (ISO 7380 style): a pan head touches a 12 mm wide USB-C plug in the XIAO when the cover is off.

Board coordinates are seen from the front (switch side, facing the cover). +x is the rider's right, +y is down the facet, away from button C.

## Circuit

| Net | Front | Rear |
|---|---|---|
| UP, DOWN, LEFT, RIGHT | One pad of each switch | Wire pads U, D, L, R to XIAO D3, D4, D5, D6 |
| GND | The diagonally opposite pad of each switch | Wire pad G to XIAO GND; input pad GND |
| VIN | — | Input pad VIN, through F1 |
| +5V | — | After F1; clamped by D1; wire pad 5V to the XIAO 5V pin |

- **Switches.** Each switch uses one diagonal pair of its four pads. Whether the part pairs pads 1-2 or 1-3 internally, a diagonal pair always spans the contact, so the internal pairing does not need to be confirmed. The other two pads are soldered but not connected.
- **Centre press.** There is no fifth switch. Pushing the stick straight in closes all four; the firmware reads the chord as the centre press (see the [firmware specification](../../docs/firmware-spec.md)).
- **F1.** Bourns MF-MSMF050-2, PTC resettable fuse, 1812: 0.5 A hold, 1 A trip, 15 V maximum.
- **D1.** Littelfuse SMBJ5.0A, unidirectional TVS, 600 W, 5.0 V stand-off. It clamps transients on the supply. If the supply is reversed, it conducts forward and F1 trips. The 15 V rating of F1 also covers a supply wired to 12 V by mistake; 6 V polyfuses, common in 1206, would not.
- The XIAO takes its supply from the 5V wire pad, not from the cable directly. In Seeed's XIAO nRF52840 V1.2 schematic (KiCad project dated 2026-08-28, from the Seeed wiki), the 5V header pin is the same net as the USB-C VBUS pins, with no diode or switch between them. The Schottky diode on the XIAO sits after that net, in front of its 3.3 V regulator. So the bike supply and a USB-C cable would be connected straight together, and each could feed current into the other. F1 limits that current to its 0.5 A hold rating, but that is still enough to stress a computer's USB port or the bike's socket. Do not connect USB-C while the bike supply is connected. The board revision bought may differ from V1.2; check its silkscreen.

## Placement against the enclosure

The CAD checks the PCB against the housing, cover, gasket, plate, stick, XIAO and USB-C plug:
- Front: the switch bodies and pads; the two standoffs clear the pads.
- Rear, everywhere: 1.0 mm for solder joints, vias and screw heads (1.1 mm).
- Rear, upper half (towards button C) and the two side strips |x| ≥ 6.3 mm: 3.0 mm. All rear parts and wire pads are in these zones. The lower middle stays low because a USB-C plug in the XIAO (cover off) passes close behind it.

Route the supply cable from the gland along the side wall to the VIN and GND pads, and the six XIAO wires from the top edge.

## Parts

| Ref | Part | LCSC | Side |
|---|---|---|---|
| SW1–SW4 | C&K KSC221JLFS, sealed tact switch, 2 N | C221726 | Front |
| F1 | Bourns MF-MSMF050-2 | C17313 | Rear |
| D1 | Littelfuse SMBJ5.0A | C83333 | Rear |
| J1, J2 | Wire pads (no part) | — | Rear |

The LCSC numbers were checked against the LCSC listings and the EasyEDA part data on 2026-10-10; stock and prices change.

The switches were the KSC222JLFS (C221728) until 2026-10-13, when LCSC had none in stock. The KSC221JLFS has the same force, body and J-bend land pattern (C&K KSC datasheet, B-50 and B-52), so the board did not change. It has standard instead of long-life silver contacts (500,000 instead of 1,000,000 operations) and up to 0.65 mm travel instead of 0.5 mm; the knob push gap in the V0.24 CAD grew to 0.9 mm to match. The KSC222JLFS still fits if it is sourced elsewhere.

The KSC2 land pattern comes from the LCSC/EasyEDA footprint for C221728; C&K gives one J-bend pad layout for the whole KSC2 range. Its pads reach 0.95 mm beyond the body, so the joints can be reached with a fine iron tip or hot air.

## Fabrication files

`fab/` holds the outputs for the current board:
- `joystick-gerbers.zip` and `gerbers/`: copper, mask, paste, silkscreen, outline, and separate plated and non-plated Excellon drill files.
- `joystick-bom.csv`: grouped BOM with MPN and LCSC numbers.
- `joystick-pos.csv`: placement file (KiCad format, mm). JLCPCB expects its own column names and often needs rotation corrections for some parts; check the placement preview before ordering assembly.
- `joystick-schematic.pdf`.

Assembly on both sides costs more at most assembly services. Ordering assembly of the front (four switches) and hand-soldering F1 and D1 on the rear is the cheaper option; both are large parts.

## Regenerating

The board and schematic are generated by script, so the CAD numbers and the KiCad files stay in step. Edit `design.py` (placement, nets, routing), then run from this directory:

```
/Applications/KiCad/KiCad.app/Contents/Frameworks/Python.framework/Versions/Current/bin/python3 gen_pcb.py
```

`gen_pcb.py` writes `joystick.kicad_pcb` and calls `gen_sch.py` for `joystick.kicad_sch`. Then check and export:

```
K=/Applications/KiCad/KiCad.app/Contents/MacOS/kicad-cli
$K sch erc --severity-all joystick.kicad_sch
$K pcb drc --schematic-parity --severity-all joystick.kicad_pcb
$K pcb export gerbers --layers F.Cu,B.Cu,F.Paste,B.Paste,F.SilkS,B.SilkS,F.Mask,B.Mask,Edge.Cuts --subtract-soldermask -o fab/gerbers/ joystick.kicad_pcb
$K pcb export drill --format excellon --excellon-separate-th --generate-map --map-format gerberx2 -o fab/gerbers/ joystick.kicad_pcb
$K pcb export pos --format csv --units mm --side both --exclude-dnp -o fab/joystick-pos.csv joystick.kicad_pcb
$K sch export bom --fields 'Reference,Value,Footprint,Manufacturer,MPN,LCSC,${QUANTITY}' --labels 'Reference,Value,Footprint,Manufacturer,MPN,LCSC,Qty' --group-by 'Value,Footprint' --exclude-dnp -o fab/joystick-bom.csv joystick.kicad_sch
```

Tested with KiCad 10.0.6 on macOS. Run without a configured KiCad (no global library tables), ERC and DRC also report that the stock `Fuse`, `Diode_SMD` and symbol libraries are not configured; those warnings go away once KiCad has been opened once and has created its default tables.

The project tables (`fp-lib-table`, `sym-lib-table`) add the local `orr` library: the KSC2 footprint and 3D model, the wire-pad footprints, the standoff hole and the KSC221JLFS symbol.

## Open points

- Measure the switch height on the real parts: together with the printed plate, ball, disc and standoffs it sets the 0.05 mm rest gap under the disc.
- Decide whether to add a series Schottky diode after F1, so that USB-C can stay connected with the bike supply on. It would cost about 0.3–0.4 V at the XIAO, ahead of its own diode and regulator, and it needs a place on the rear of the board.
- Check the placement file rotations with the assembler's preview.

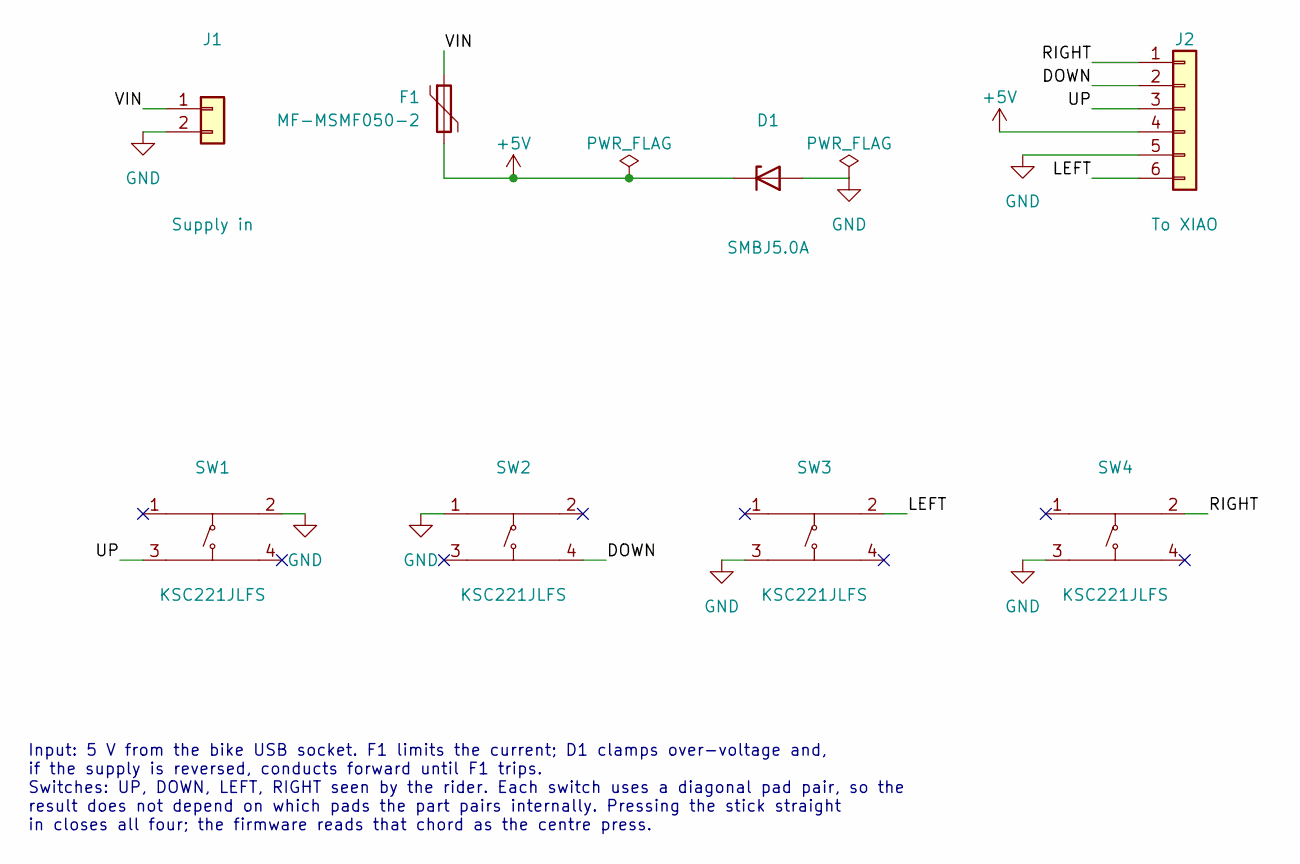
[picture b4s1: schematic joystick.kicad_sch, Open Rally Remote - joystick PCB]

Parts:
D1: SMBJ5.0A; D_SMB; MPN SMBJ5.0A; LCSC C83333
F1: MF-MSMF050-2; Fuse_1812_4532Metric; MPN MF-MSMF050-2; LCSC C17313
J1: Supply in; WirePads_1x02_P2.4mm
J2: To XIAO; WirePads_1x06_P2.1mm
SW1, SW2, SW3, SW4: KSC221JLFS; KSC2_SMD_6.2x6.2mm; MPN KSC221JLFS; LCSC C221726

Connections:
+5V: D1.1 (K), F1.2, J2.4
/DOWN: J2.2, SW2.4
/LEFT: J2.6, SW3.2
/RIGHT: J2.1, SW4.2
/UP: J2.3, SW1.3
/VIN: F1.1, J1.1
GND: D1.2 (A), J1.2, J2.5, SW1.2, SW2.1, SW3.3, SW4.3

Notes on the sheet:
Input: 5 V from the bike USB socket. F1 limits the current; D1 clamps over-voltage and, if the supply is reversed, conducts forward until F1 trips. Switches: UP, DOWN, LEFT, RIGHT seen by the rider. Each switch uses a diagonal pad pair, so the result does not depend on which pads the part pairs int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
